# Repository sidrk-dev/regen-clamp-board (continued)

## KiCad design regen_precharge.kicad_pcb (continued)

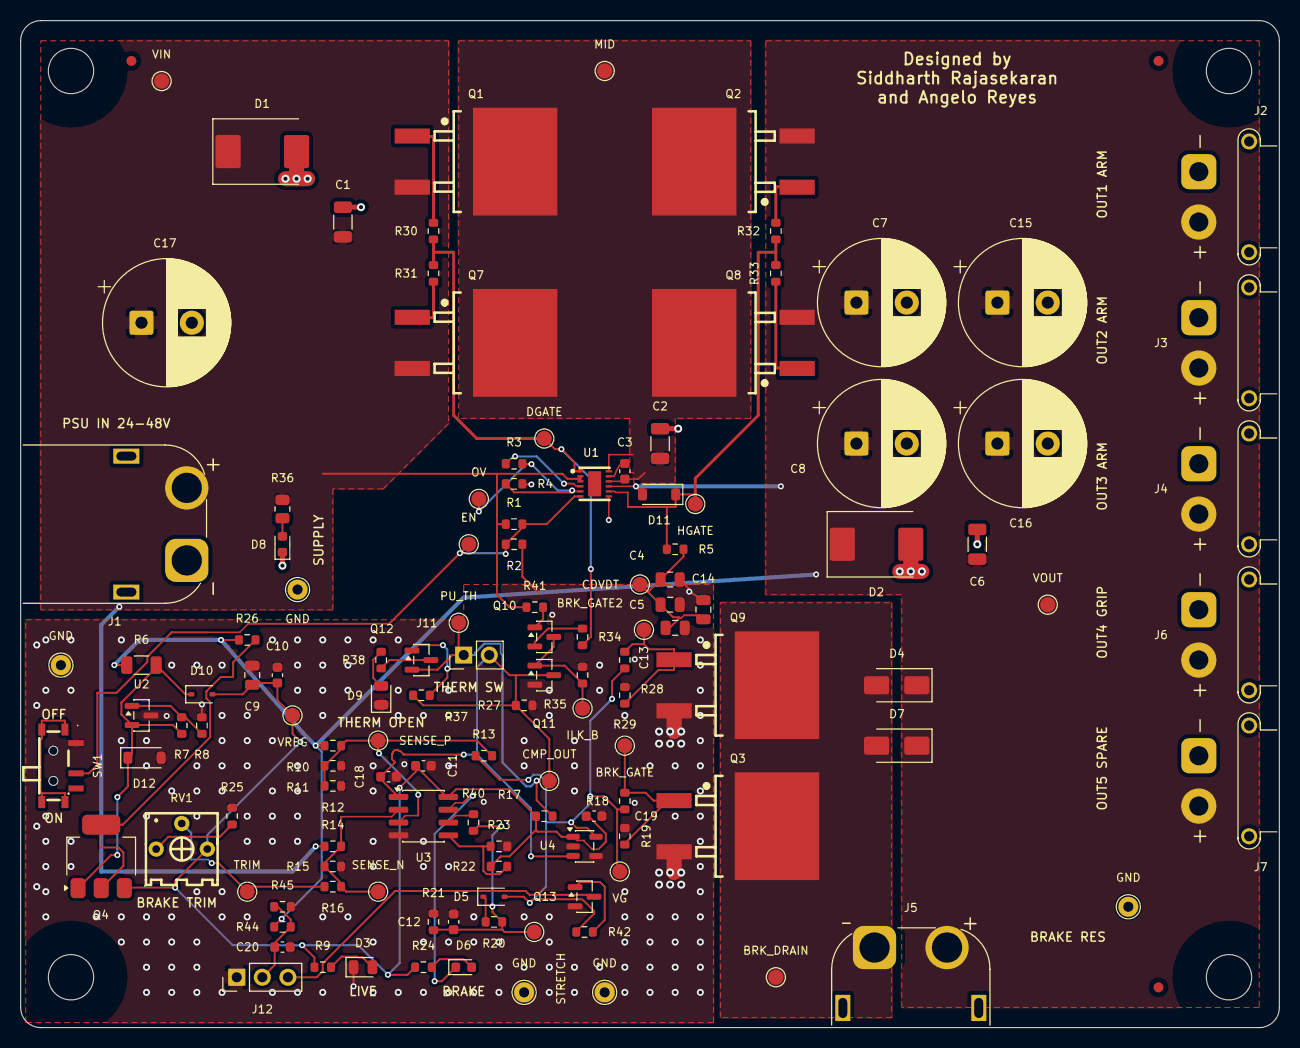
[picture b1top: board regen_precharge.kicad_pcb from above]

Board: 2 copper layers, 125.0 x 100.0 mm, 133 parts (0 on the bottom side), 46 nets.

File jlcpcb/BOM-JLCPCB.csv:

Comment,Designator,Footprint,LCSC Part #
1uF 50V,"C3,C19",C_0603_1608Metric,C15849
100nF 100V,"C4,C5,C13,C14",C_0805_2012Metric,C28233
10uF 25V,C9,C_0805_2012Metric,C15850
100nF,"C10,C11,C12,C20",C_0603_1608Metric,C14663
1nF 50V,C18,C_0603_1608Metric,C1588
SMCJ51A TVS,"D1,D2",D_SMC,C42371549
GREEN (output live),D3,LED_0805_2012Metric,C2297
SS210,"D4,D7",D_SMA,C14996
1N4148WS,"D5,D10",D_SOD-323,C2128
RED (regen brake active),D6,LED_0603_1608Metric,C2286
WHITE (supply present),D8,LED_0603_1608Metric,C2290
YELLOW (thermal loop open),D9,LED_0805_2012Metric,C2296
BZT52C12,D11,D_SOD-123,C2932744
BZT52C16,D12,D_SOD-123,C19077413
CRSS042N10N,"Q1,Q2,Q3,Q7,Q8,Q9",TO-263-3_L10.2-W10.7-P5.08-LS16.2-TL,C410926
BCP56-16,Q4,SOT-223,C41375109
MMBT5401,Q10,SOT-23,C8326
MMBT3904,Q11,SOT-23,C20526
S8550,Q12,SOT-23,C105432
2N7002,Q13,SOT-23,C8545
1M,"R1,R37",R_0603_1608Metric,C22935
100k,"R2,R3,R27,R35,R40,R44",R_0603_1608Metric,C25803
2.2k,"R4,R38",R_0603_1608Metric,C4190
1k,"R5,R42",R_0603_1608Metric,C21190
10k 1206,R6,R_1206_3216Metric,C17902
39k,R7,R_0603_1608Metric,C23153
10k,"R8,R9,R19,R23,R29,R41",R_0603_1608Metric,C25804
100k 0.1%,"R10,R14",R_0603_1608Metric,C122538
20k 0.1%,"R11,R15",R_0603_1608Metric,C723637
220k,R12,R_0603_1608Metric,C22961
510k (hysteresis),R13,R_0603_1608Metric,C23192
150k (offset),R16,R_0603_1608Metric,C22807
4.7k,"R17,R24",R_0603_1608Metric,C23162
10R,"R18,R28,R30,R31,R32,R33",R_0603_1608Metric,C22859
100R,R20,R_0603_1608Metric,C22775
2M,R21,R_0603_1608Metric,C22976
47k,"R22,R34",R_0603_1608Metric,C25819
6.8k,R25,R_0603_1608Metric,C23212
470R,R26,R_0603_1608Metric,C23179
33k 0805,R36,R_0805_2012Metric,C17633
5.6k,R45,R_0603_1608Metric,C23189
LM74800QDRRRQ1,U1,WSON-12_L3.0-W3.0-P0.50-TL-EP-2,C3215600
CJ431,U2,SOT-23,C3113
LM393,U3,SOIC-8_3.9x4.9mm_P1.27mm,C7955
UCC27517,U4,SOT-23-5,C99395

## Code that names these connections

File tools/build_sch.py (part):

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part("R5", "Device:R", "1k", R0603, "C21190", 160, 105, {"1": "HGATE", "2": "CDVDT"})
# D11: the 400 nF on CDVDT holds HGATE up when VOUT falls fast; HGATE-OUT is 15 V absolute maximum. R5 limits the current to under 50 mA.
# Rev E review additions:
# R40 limits current into U3 pin 6 if the rail collapses while C12 still holds the stretch voltage (LM393 input max = supply).
part("R40", "Device:R", "100k", R0603, "C25803", 580, 100, {"1": "STRETCH", "2": "STRETCH_IN"})
# R41: with a reversed supply and D1 open, nothing else limits current through Q10's base-collector and Q11's base-emitter.
part("R41", "Device:R", "10k", R0603, "C25804", 580, 130, {"1": "VIN", "2": "ILK_BASE"})
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part("R14", "Device:R", "100k 0.1%", R0603, "C122538", 150, 225, {"1": "VIN", "2": "SENSE_N"})
part("R15", "Device:R", "20k 0.1%", R0603, "C723637", 150, 255, {"1": "SENSE_N", "2": "GND"})
part("R16", "Device:R", "150k (offset)", R0603, "C22807", 165, 240, {"1": "TRIM", "2": "SENSE_N"}, rot=90)
part("RV1", "Device:R_Potentiometer", "10k trim: brake threshold", "jlc:RES-ADJ-TH_3362P", "C58159", 120, 245, {"1": "TRIM_LO", "2": "TRIM", "3": "VREG"}, note="Hand-solder")  # 3362P: pin 3 is the clockwise end, so clockwise raises the threshold
part("R25", "Device:R", "6.8k", R0603, "C23212", 135, 260, {"1": "TRIM_LO", "2": "GND"})
part("U3", "Comparator:LM393", "LM393", "Package_SO:SOIC-8_3.9x4.9mm_P1.27mm", "C7955", 195, 205, {"1": "CMP_OUT", "2": "SENSE_N", "3": "SENSE_P"}, unit=1)
part("U3", "Comparator:LM393", "LM393", "Package_SO:SOIC-8_3.9x4.9mm_P1.27mm", "C7955", 345, 220, {"5": "LED_REF", "6": "STRETCH_IN", "7": "LEDR_K"}, unit=2)
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# U4 replaces the Q5/Q6 BJT totem pole: 4 A each way, so the brake switches in tens of ns instead of about 0.5 us,
# and the LM393 no longer sinks Q6's base current. Input high above 2.4 V, low below 1.0 V (TI datasheet).
part("U4", "jlc:UCC27517DBV", "UCC27517", "Package_TO_SOT_SMD:SOT-23-5", "C99395", 235, 195, {"1": "VREG", "2": "GND", "3": "CMP_OUT", "4": "GND", "5": "VG"})
# Telemetry for a microcontroller: J12 pin 1 GND, pin 2 BUS_ADC (VOUT x 0.053, 3.3 V at 62 V), pin 3 BRK_FLAG (open drain, low while braking)
part("R44", "Device:R", "100k", R0603, "C25803", 640, 100, {"1": "VOUT", "2": "BUS_ADC"})
part("R45", "Device:R", "5.6k", R0603, "C23189", 640, 130, {"1": "BUS_ADC", "2": "GND"})
part("C20", "Device:C", "100nF", C0603, "C14663", 660, 130, {"1": "BUS_ADC", "2": "GND"})
part("R42", "Device:R", "1k", R0603, "C21190", 660, 100, {"1": "VG", "2": "FLAG_G"})
part("Q13", "Transistor_FET:2N7002", "2N7002", SOT23, "C8545", 680, 100, {"1": "FLAG_G", "2": "GND", "3": "BRK_FLAG"})
part("J12", "Connector_Generic:Conn_01x03", "MCU: GND / BUS_ADC / BRK_FLAG", "Connector_PinHeader_2.54mm:PinHeader_1x03_P2.54mm_Vertical", "C2937625", 700, 100, {"1": "GND", "2": "BUS_ADC", "3": "BRK_FLAG"}, note="Hand-solder")
part("R18", "Device:R", "10R", R0603, "C22859", 255, 205, {"1": "VG", "2": "BRK_GATE"}, rot=90)
part("R19", "Device:R", "10k", R0603, "C25804", 270, 225, {"1": "BRK_GATE", "2": "GND"})
part("Q3", "jlc:CRSS042N10N", "CRSS042N10N (brake)", FET, "C410926", 285, 200, {"1": "BRK_GATE", "2": "BRK_DRAIN", "3": "GND"})
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part("R29", "Device:R", "10k", R0603, "C25804", 455, 185, {"1": "BRK_GATE2", "2": "GND"})
part("Q9", "jlc:CRSS042N10N", "CRSS042N10N (brake 2)", FET, "C410926", 475, 165, {"1": "BRK_GATE2", "2": "BRK_DRAIN", "3": "GND"})
part("D7", "Device:D_Schottky", "SS210", "Diode_SMD:D_SMA", "C14996", 495, 140, {"1": "VOUT", "2": "BRK_DRAIN"}, rot=90)
part("J11", "Connector_Generic:Conn_01x02", "Brake resistor thermal switch (NC) or jumper", "Connector_PinHeader_2.54mm:PinHeader_1x02_P2.54mm_Vertical", "C492401", 450, 225, {"1": "PU_TH", "2": "CMP_OUT"}, note="Hand-solder")
part("R27", "Device:R", "100k", R0603, "C25803", 470, 235, {"1": "CMP_OUT", "2": "GND"})

# ---- Block 7 (rev C): individual gate resistors for the paralleled FETs ----
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
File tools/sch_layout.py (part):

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    W(("R33", 1), ("Q8", 1)); plabel("R33", 2); lbl("HG8", (185.42, YP2 + 6.35), 0)

    # U1, left side: DGATE, VIN, OV divider, EN
    at("U1", 304.8, 101.6, 0)                        # left pins x 290.83: 1 DGATE 96.52 ... 6 EN 109.22
    W(("U1", 2), ("U1", 3)); plabel("U1", 2); plabel("U1", 1)
    at("R3", 264.16, 107.95, 0)
    at("R4", 264.16, 119.38, 0); gpin("R4", 2)
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        W((x, YP), (ref, 1)); gpin(ref, 2)
    xs = [571.5 + 35.56 * i for i in range(5)]
    for x, ref in zip(xs, ("J2", "J3", "J4", "J6", "J7")):
        at(ref, x, 86.36, 180)                       # pin 2 VOUT (x+5.08, 83.82), pin 1 GND (x+5.08, 86.36)
        W((x + 10.16, YP), (x + 10.16, 83.82), (ref, 2)); gpin(ref, 1)
    W(("Q2", 3), (xs[-1] + 10.16, YP))

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    W(("U4", 5), (594.36, 218.44), (594.36, YQ)); lbl("VG", (581.66, 218.44), 90)
    at("Q3", 614.68, YQ, 0); at("R18", 601.98, YQ, 90)
    W((594.36, YQ), ("R18", 1)); W(("R18", 2), ("Q3", 1)); gpin("Q3", 3)
    at("R19", 608.33, 254.0, 0); W((608.33, YQ), ("R19", 1)); gpin("R19", 2); lbl("BRK_GATE", (608.33, YQ), 90)
    at("Q9", 662.94, YQ, 0); at("R28", 650.24, YQ, 90)
    plabel("R28", 1); W(("R28", 2), ("Q9", 1)); gpin("Q9", 3)
    at("R29", 656.59, 254.0, 0); W((656.59, YQ), ("R29", 1)); gpin("R29", 2); lbl("BRK_GATE2", (656.59, YQ), 90)
    YBD = 226.06
    at("J5", 731.52, YBD, 0)                         # 1 BRK_DRAIN (726.44, YBD), 2 VOUT (726.44, YBD + 2.54)
    W(("Q3", 2), (615.95, YBD), ("J5", 1)); W(("Q9", 2), (664.21, YBD))
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
    # ================= INTERLOCK
    at("Q10", 55.88, 350.52, 180)                    # E (53.34, 345.44) up, C (53.34, 355.6) down, B (60.96, 350.52)
    at("R34", 53.34, 337.82, 0); plabel("R34", 1); W(("R34", 2), ("Q10", 2)); lbl("ILK_E", (53.34, 342.9), 180)
    at("R41", 68.58, 340.36, 0); plabel("R41", 1)
    W(("R41", 2), (68.58, 350.52), ("Q10", 1)); lbl("ILK_BASE", (63.5, 350.52), 90)
    at("R35", 53.34, 367.03, 0); W(("Q10", 3), ("R35", 1)); gpin("R35", 2)
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    # ================= THERM OPEN LED
    at("Q12", 205.74, 350.52, 180)                   # E up (203.2, 345.44), B right (210.82, 350.52), C down (203.2, 355.6)
    plabel("Q12", 2)
    at("R37", 220.98, 350.52, 270); W(("R37", 2), ("Q12", 1)); plabel("R37", 1); lbl("THB", (213.36, 350.52), 270)
    at("R38", 203.2, 363.22, 0); W(("Q12", 3), ("R38", 1)); lbl("THC", (203.2, 358.14), 180)
    at("D9", 203.2, 375.92, 90); W(("R38", 2), ("D9", 2)); gpin("D9", 1); lbl("LEDT_A", (203.2, 369.57), 0)

    # ================= RED BRAKE LED
    Y0 = 345.44
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    W(("J12", 2), (680.72, 353.06)); lbl("BUS_ADC", (640.08, 353.06), 90)
    at("C20", 670.56, 360.68, 0); W((670.56, 353.06), ("C20", 1)); gpin("C20", 2)
    at("Q13", 650.24, 381.0, 0)                      # gate (645.16, 381), D (652.78, 375.92), S (652.78, 386.08)
    at("R42", 637.54, 381.0, 90); plabel("R42", 1); W(("R42", 2), ("Q13", 1)); lbl("FLAG_G", (643.89, 381.0), 90)
    plabel("Q13", 3); gpin("Q13", 2)

    # ================= TEST POINTS, HOLES, FIDUCIALS, FLAGS
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
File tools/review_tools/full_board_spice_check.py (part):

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.ends UCC27517

* === Pin-Accurate LM74800-Q1 Datasheet Macromodel ===
* Pins: 1:DGATE 2:A 3:VSNS 4:SW 5:OV 6:EN_UVLO 7:GND 8:HGATE 9:OUT 10:VS 11:CAP 12:C
.subckt LM74800_Q1 DGATE A VSNS SW OV EN_UVLO GND HGATE OUT VS CAP C params: ICAP_MA=2.7 IHG_UA=55 STRICT_177MV=1 VAC_FWD_MV=177
.model SW_EN   SW(Vt=0.705  Vh=0.035  Ron=10 Roff=1e7)
.model SW_UVLO SW(Vt=1.1815 Vh=0.0495 Ron=10 Roff=1e7)
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
D5   vg str_d D4148
R20  str_d stretch 100
C12  stretch 0 100n IC=0
R21  stretch 0 2meg
R40  stretch stretch_in 100k
R22  vreg led_ref 47k
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
R44  vout bus_adc 100k
R45  bus_adc 0 5.6k
C20  bus_adc 0 100n IC=0
R42  vg flag_g 1k
M13  brk_flag flag_g 0 0 NFET_2N7002
RPU_MCU v_mcu brk_flag 10k
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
